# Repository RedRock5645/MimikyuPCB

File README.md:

# MimikyuPCB
Slack username: Red Rock

## Description
 A hack club soldering project! I'm making a mimikyu key chain whose real eyes will light up depending on the light and its body will vibrate. I really like pokemon, so that's the inspiration behind the design. 

## Materials
 - 2x 5mm LEDs (same color hopefully)
 - 3x 220ohms resistors
 - 1x mini motor disc
 - 1x photoresister
 - 1x 6microfarad capacitor
 - 2x 6mm push button
 - 1x battery cell
 - 1x NPN transistor

## ScreenShots

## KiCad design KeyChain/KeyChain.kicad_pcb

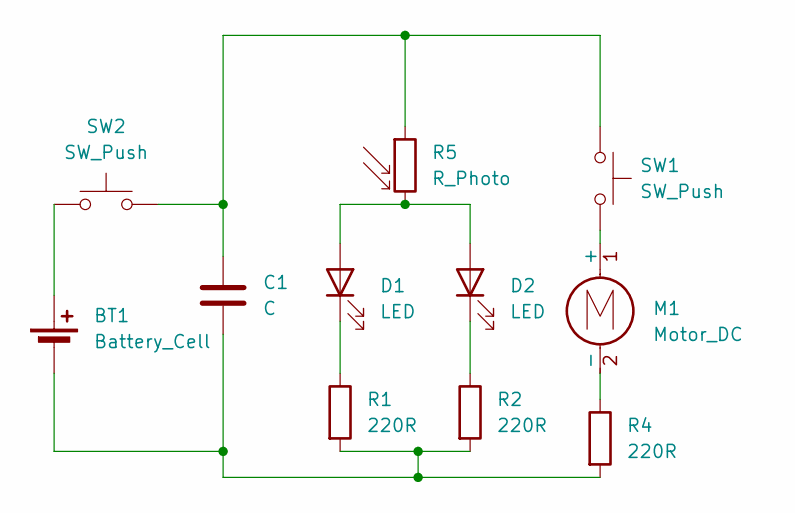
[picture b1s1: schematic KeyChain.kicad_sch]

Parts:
BT1: Battery_Cell; BatteryHolder_Keystone_3034_1x20mm
C1: C; CP_Radial_D8.0mm_P5.00mm
D1, D2: LED; LED_D5.0mm
M1: Motor_DC; PinHeader_1x02_P2.54mm_Vertical
R1, R2, R4: 220R; R_Axial_DIN0207_L6.3mm_D2.5mm_P7.62mm_Horizontal
R5: R_Photo; R_LDR_5.1x4.3mm_P3.4mm_Vertical
SW1, SW2: SW_Push; SW_PUSH_6mm

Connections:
unnamed: BT1.1 (+), SW2.1
unnamed: BT1.2 (-), C1.2, R1.2, R2.2, R4.2
unnamed: C1.1, R5.1, SW1.1, SW2.2
unnamed: D1.2 (A), D2.2 (A), R5.2
unnamed: D1.1 (K), R1.1
unnamed: D2.1 (K), R2.1
unnamed: M1.1 (+), SW1.2
unnamed: M1.2 (-), R4.1

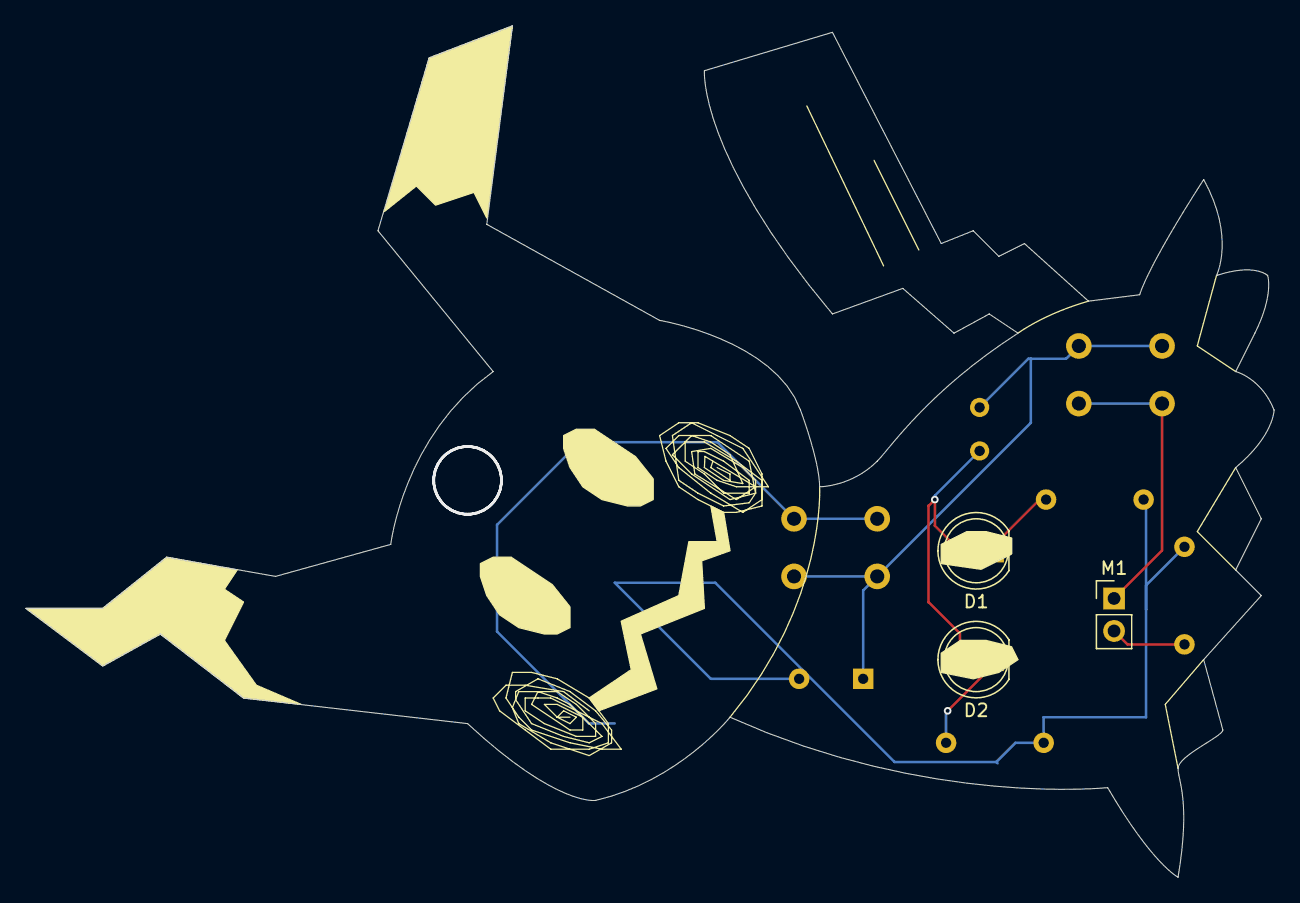
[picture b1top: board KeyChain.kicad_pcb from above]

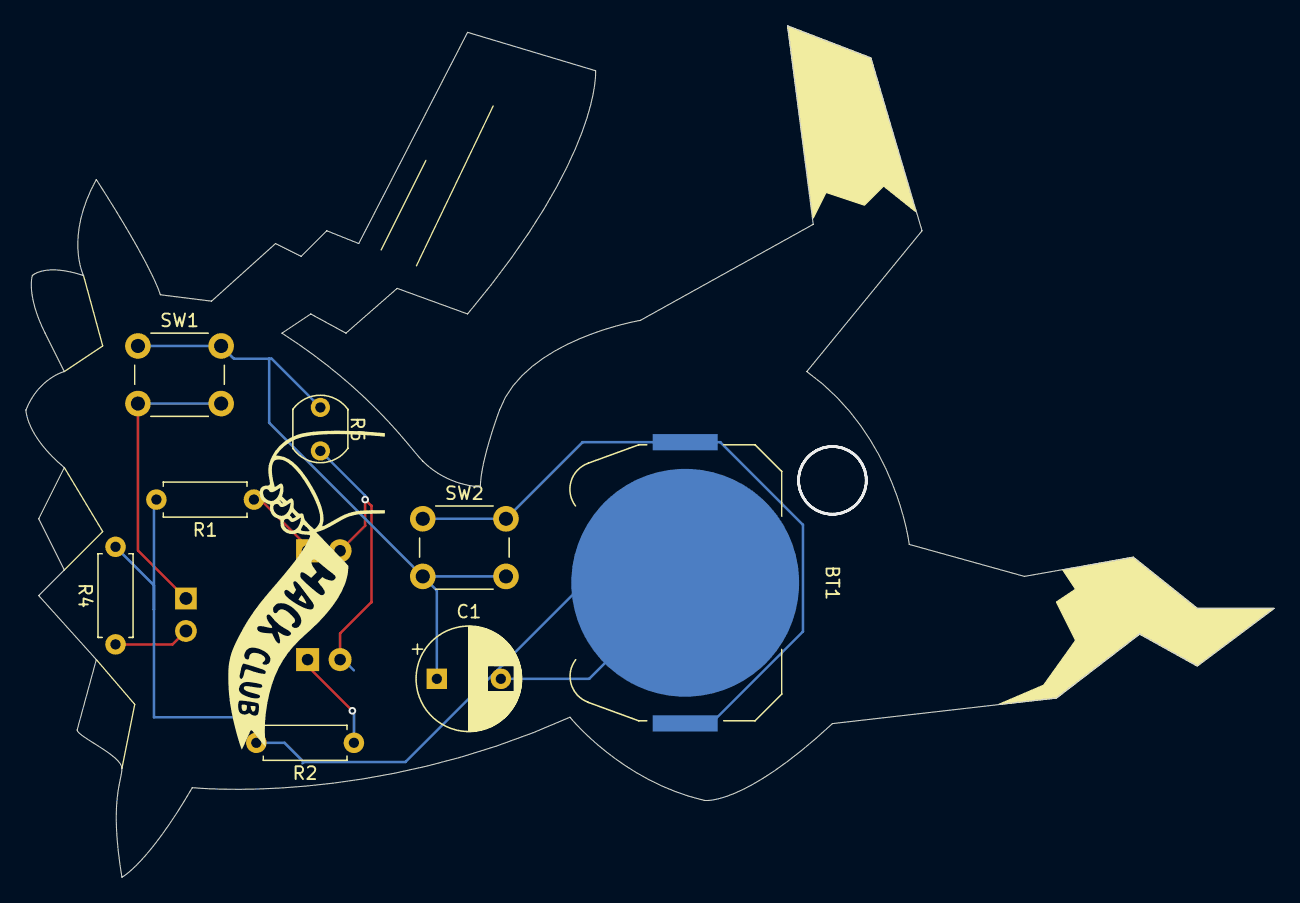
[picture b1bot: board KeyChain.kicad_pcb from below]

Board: 2 copper layers, 97.5 x 66.5 mm, 11 parts (8 on the bottom side), 8 nets.

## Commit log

2025-05-02 Mimikyu Key chain done!!!!!!!!
2025-05-02 Added read me and images
2025-05-09 updated photos
2025-05-09 I think this is the correct folder
